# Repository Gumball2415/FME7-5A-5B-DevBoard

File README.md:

# FME7/S5A/S5B Development/Reproduction Cartridge Board

An Open-Source HardWare (OSHW) development/reproduction cartridge PCB designed for INES mapper 69.

## PCB Specifications

Note that this project is optimized for JLCPCB manufacturing, so you may have to modify the gerber export, remove the "JLCJLCJLCJLC" silkscreen text, etc.

- 2 layers
- 92mm x 56.7mm
- 1.20mm thickness
- ENIG-RoHS surface finish recommended; Gold fingers optional
- Light silkscreen, dark soldermask

## License

The PCB and schematics are licensed under the TAPR Open Hardware License ([www.tapr.org/OHL](http://www.tapr.org/OHL)). © Persune 2021

## Credits

- Lockster - Help and assistance with schematics
- lidnariq - Clarification on FME7 connections
- yoeynsf - Pixel art of Dagga
- plgDavid - Inspiration
- Special thanks to the NESDEV community, this project wouldn't have been possible without their extensive help and wiki.

## Support

Support me on [Ko-Fi](https://ko-fi.com/persune) to help me afford hardware development equipment and further improve this project!

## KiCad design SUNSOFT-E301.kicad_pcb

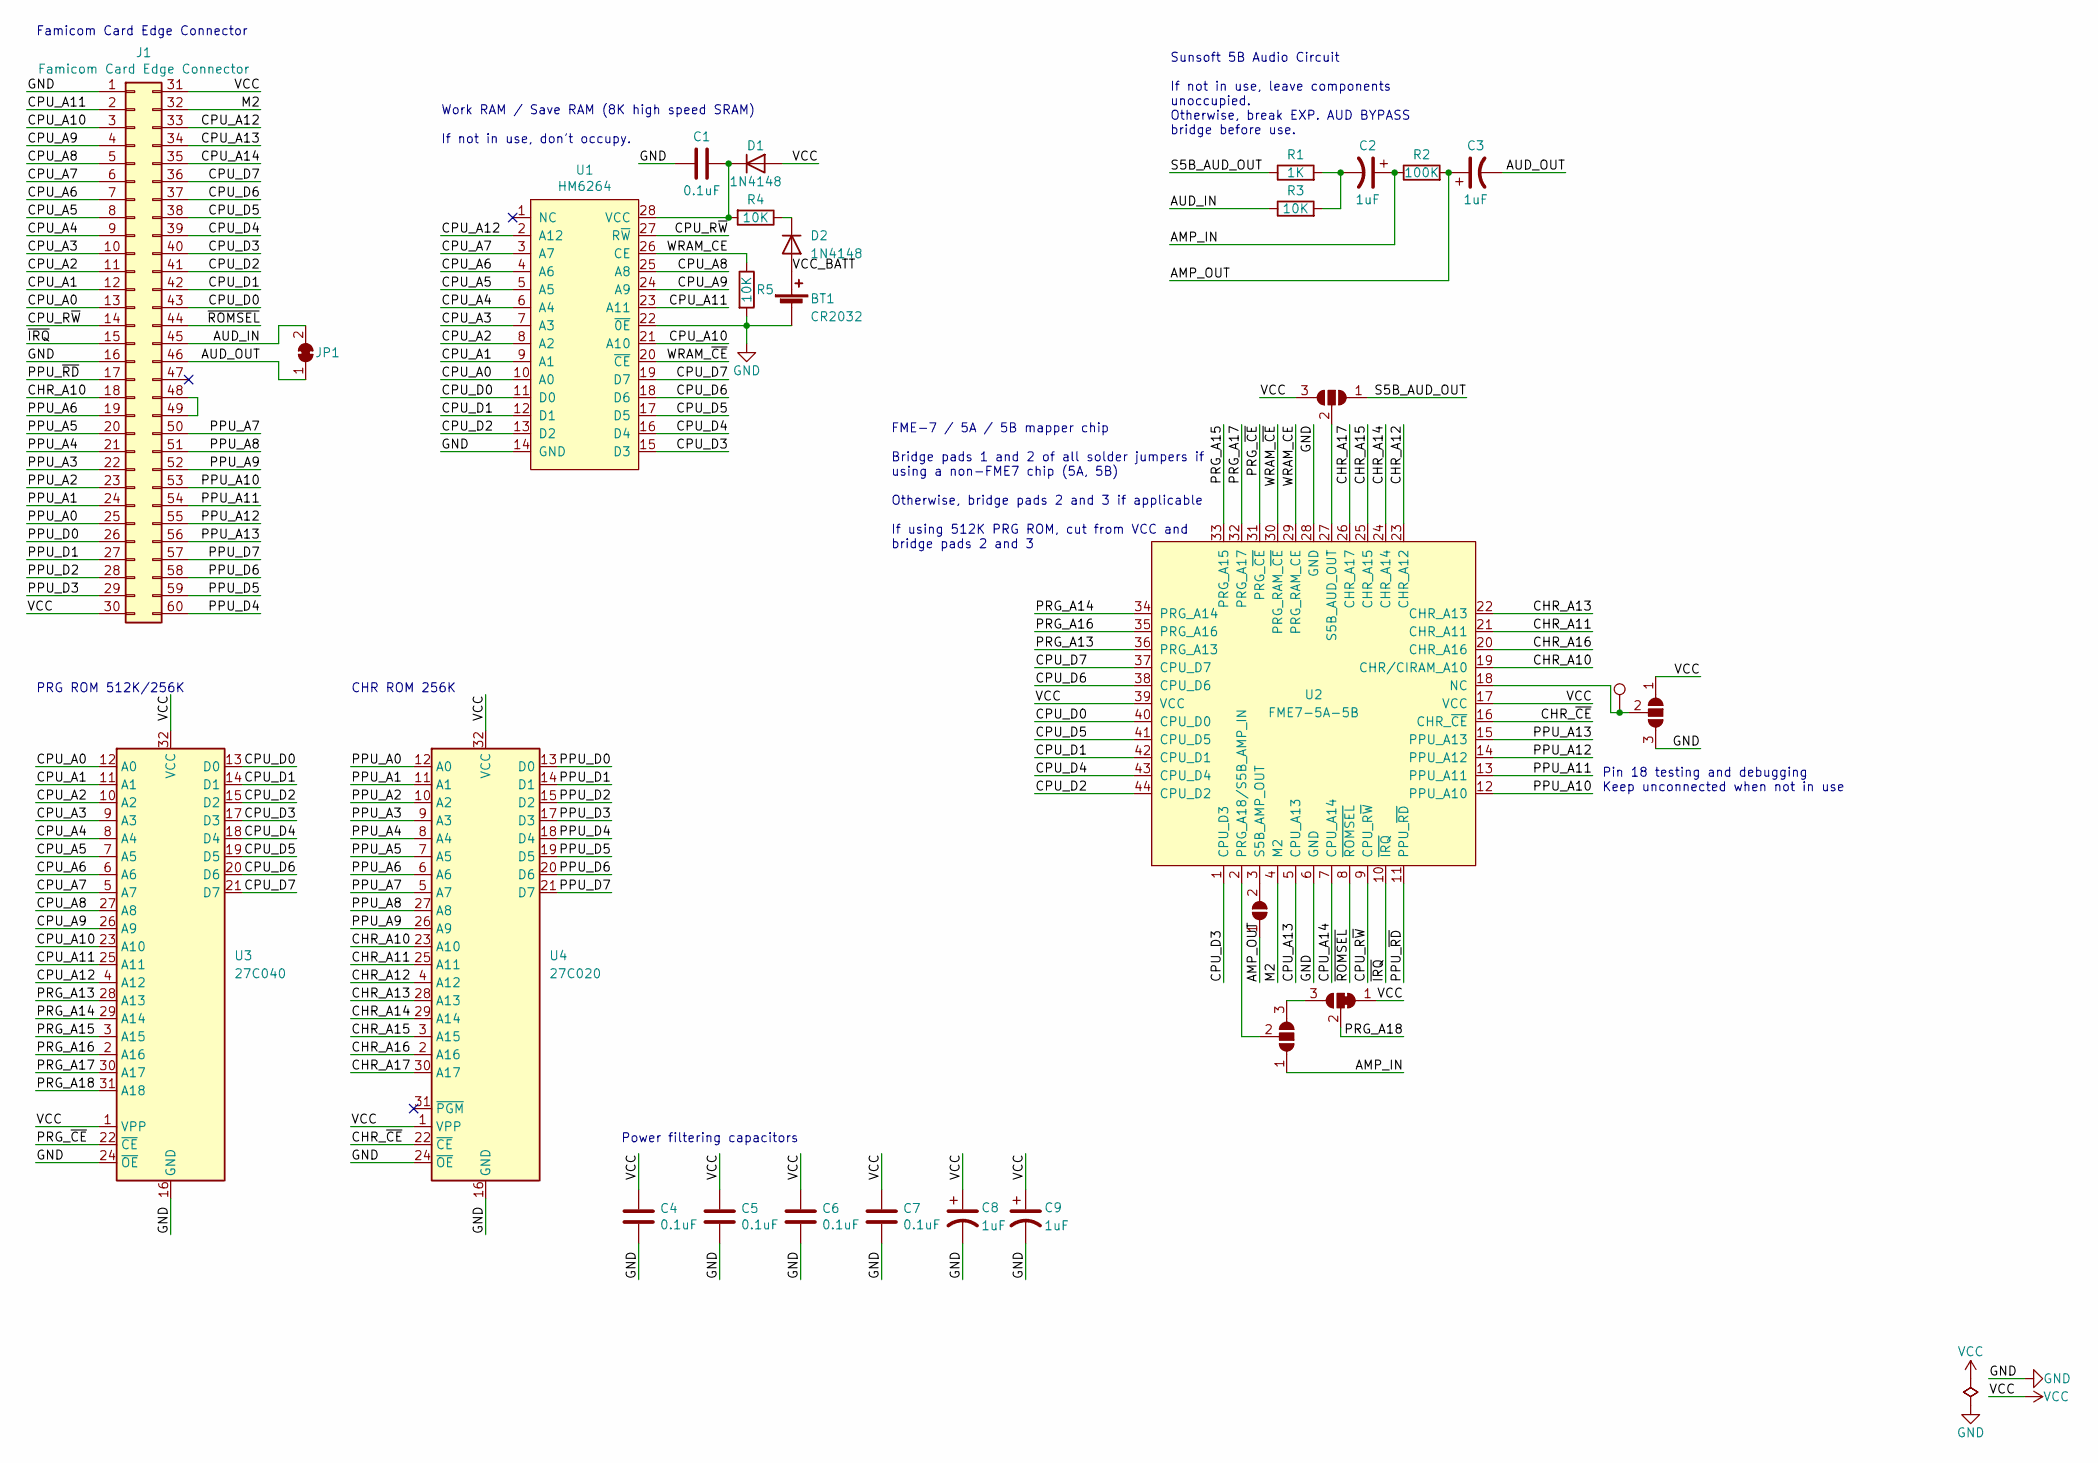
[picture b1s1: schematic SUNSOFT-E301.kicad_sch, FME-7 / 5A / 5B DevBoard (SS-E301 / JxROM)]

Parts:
BT1: CR2032; BS-02-A1AK006; LCSC C964746
C1, C4, C5, C6, C7: 0.1uF; C_0805_2012Metric; LCSC C779984
C2, C3, C8, C9: 1uF; CP_Elec_4x5.3; LCSC C249445
D1, D2: 1N4148; D_SOD-123; LCSC C2099
J1: Famicom Card Edge Connector; BBW-E301
JP1: SolderJumper_2_Bridged; SolderJumper-2_P1.3mm_Bridged_RoundedPad1.0x1.5mm
JP2, JP4, JP5: SolderJumper-3_P1.3mm_Open_RoundedPad1.0x1.5mm
JP3: SolderJumper-2_P1.3mm_Open_RoundedPad1.0x1.5mm
JP6: SolderJumper-3_P1.3mm_Bridged12_RoundedPad1.0x1.5mm
R1: 1K; R_0805_2012Metric; LCSC C441949
R2: 100K; R_0805_2012Metric; LCSC C441960
R3, R4, R5: 10K; R_0805_2012Metric; LCSC C441955
TP1: TestPoint_Pad_D1.0mm
U1: HM6264; DIP-28_W15.24mm; LCSC C72121
U2: FME7-5A-5B; Sunsoft-5
U3: 27C040; DIP-32_W15.24mm_Socket; LCSC C72122
U4: 27C020; DIP-32_W15.24mm_Socket; LCSC C72122

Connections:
/AMP_IN: C2.1, JP2.1 (A), R2.1
/AMP_OUT: C3.1, JP3.1 (A), R2.2
/AUD_IN: J1.45, JP1.2 (B), R3.1
/AUD_OUT: C3.2, J1.46, JP1.1 (A)
/CHR_A10: J1.18, U2.19 (CHR/CIRAM_A10), U4.23 (A10)
/CHR_A11: U2.21 (CHR_A11), U4.25 (A11)
/CHR_A12: U2.23 (CHR_A12), U4.4 (A12)
/CHR_A13: U2.22 (CHR_A13), U4.28 (A13)
/CHR_A14: U2.24 (CHR_A14), U4.29 (A14)
/CHR_A15: U2.25 (CHR_A15), U4.3 (A15)
/CHR_A16: U2.20 (CHR_A16), U4.2 (A16)
/CHR_A17: U2.26 (CHR_A17), U4.30 (A17)
/CHR_~CE: U2.16 (CHR_~CE), U4.22 (~CE)
/CPU_A0: J1.13, U1.10 (A0), U3.12 (A0)
/CPU_A1: J1.12, U1.9 (A1), U3.11 (A1)
/CPU_A2: J1.11, U1.8 (A2), U3.10 (A2)
/CPU_A3: J1.10, U1.7 (A3), U3.9 (A3)
/CPU_A4: J1.9, U1.6 (A4), U3.8 (A4)
/CPU_A5: J1.8, U1.5 (A5), U3.7 (A5)
/CPU_A6: J1.7, U1.4 (A6), U3.6 (A6)
/CPU_A7: J1.6, U1.3 (A7), U3.5 (A7)
/CPU_A8: J1.5, U1.25 (A8), U3.27 (A8)
/CPU_A9: J1.4, U1.24 (A9), U3.26 (A9)
/CPU_A10: J1.3, U1.21 (A10), U3.23 (A10)
/CPU_A11: J1.2, U1.23 (A11), U3.25 (A11)
/CPU_A12: J1.33, U1.2 (A12), U3.4 (A12)
/CPU_A13: J1.34, U2.5 (CPU_A13)
/CPU_A14: J1.35, U2.7 (CPU_A14)
/CPU_D0: J1.43, U1.11 (D0), U2.40 (CPU_D0), U3.13 (D0)
/CPU_D1: J1.42, U1.12 (D1), U2.42 (CPU_D1), U3.14 (D1)
/CPU_D2: J1.41, U1.13 (D2), U2.44 (CPU_D2), U3.15 (D2)
/CPU_D3: J1.40, U1.15 (D3), U2.1 (CPU_D3), U3.17 (D3)
/CPU_D4: J1.39, U1.16 (D4), U2.43 (CPU_D4), U3.18 (D4)
/CPU_D5: J1.38, U1.17 (D5), U2.41 (CPU_D5), U3.19 (D5)
/CPU_D6: J1.37, U1.18 (D6), U2.38 (CPU_D6), U3.20 (D6)
/CPU_D7: J1.36, U1.19 (D7), U2.37 (CPU_D7), U3.21 (D7)
/CPU_R~W: J1.14, U1.27 (R~W), U2.9 (CPU_R~W)
/M2: J1.32, U2.4 (M2)
/PPU_A0: J1.25, U4.12 (A0)
/PPU_A1: J1.24, U4.11 (A1)
/PPU_A2: J1.23, U4.10 (A2)
/PPU_A3: J1.22, U4.9 (A3)
/PPU_A4: J1.21, U4.8 (A4)
/PPU_A5: J1.20, U4.7 (A5)
/PPU_A6: J1.19, U4.6 (A6)
/PPU_A7: J1.50, U4.5 (A7)
/PPU_A8: J1.51, U4.27 (A8)
/PPU_A9: J1.52, U4.26 (A9)
/PPU_A10: J1.53, U2.12 (PPU_A10)
/PPU_A11: J1.54, U2.13 (PPU_A11)
/PPU_A12: J1.55, U2.14 (PPU_A12)
/PPU_A13: J1.56, U2.15 (PPU_A13)
/PPU_D0: J1.26, U4.13 (D0)
/PPU_D1: J1.27, U4.14 (D1)
/PPU_D2: J1.28, U4.15 (D2)
/PPU_D3: J1.29, U4.17 (D3)
/PPU_D4: J1.60, U4.18 (D4)
/PPU_D5: J1.59, U4.19 (D5)
/PPU_D6: J1.58, U4.20 (D6)
/PPU_D7: J1.57, U4.21 (D7)
/PPU_~RD: J1.17, U2.11 (PPU_~RD)
/PRG_A13: U2.36 (PRG_A13), U3.28 (A13)
/PRG_A14: U2.34 (PRG_A14), U3.29 (A14)
/PRG_A15: U2.33 (PRG_A15), U3.3 (A15)
/PRG_A16: U2.35 (PRG_A16), U3.2 (A16)
/PRG_A17: U2.32 (PRG_A17), U3.30 (A17)
/PRG_A18: JP6.2 (C), U3.31 (A18)
/PRG_~CE: U2.31 (PRG_~CE), U3.22 (~CE)
/S5B_AUD_OUT: JP4.1 (A), R1.1
/VCC_BATT: BT1.1 (+), D2.2 (A)
/WRAM_CE: R5.1, U1.26 (CE), U2.29 (PRG_RAM_CE)
/WRAM_~CE: U1.20 (~CE), U2.30 (PRG_RAM_~CE)
/~IRQ: J1.15, U2.10 (~IRQ)
/~ROMSEL: J1.44, U2.8 (~ROMSEL)
GND: BT1.2 (-), C1.1, C4.2, C5.2, C6.2, C7.2, C8.2, C9.2, J1.1, J1.16, JP5.3 (B), R5.2, U1.14 (GND), U1.22 (~0E), U2.6 (GND), U2.28 (GND), U3.16 (GND), U3.24 (~OE), U4.16 (GND), U4.24 (~OE)
unnamed: C1.2, D1.1 (K), R4.2, U1.28 (VCC)
unnamed: C2.2, R1.2, R3.2
unnamed: D2.1 (K), R4.1
unnamed: J1.48, J1.49
unnamed: JP2.2 (C), U2.2 (PRG_A18/S5B_AMP_IN)
unnamed: JP2.3 (B), JP6.3 (B)
unnamed: JP3.2 (B), U2.3 (S5B_AMP_OUT)
unnamed: JP4.2 (C), U2.27 (S5B_AUD_OUT)
unnamed: JP5.2 (C), TP1.1, U2.18 (NC)
VCC: C4.1, C5.1, C6.1, C7.1, C8.1, C9.1, D1.2 (A), J1.30, J1.31, JP4.3 (B), JP5.1 (A), JP6.1 (A), U2.17 (VCC), U2.39 (VCC), U3.1 (VPP), U3.32 (VCC), U4.1 (VPP), U4.32 (VCC)

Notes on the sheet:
Sunsoft 5B Audio Circuit If not in use, leave components unoccupied. Otherwise, break EXP. AUD BYPASS bridge before use.
Power filtering capacitors
Famicom Card Edge Connector
CHR ROM 256K
FME-7 / 5A / 5B mapper chip Bridge pads 1 and 2 of all solder jumpers if using a non-FME7 chip (5A, 5B) Otherwise, bridge pads 2 and 3 if applicable If using 512K PRG ROM, cut from VCC and bridge pads 2 and 3
Work RAM / Save RAM (8K high speed SRAM) If not in use, don't occupy.
Pin 18 testing and debugging Keep unconnected when not in use
PRG ROM 512K/256K

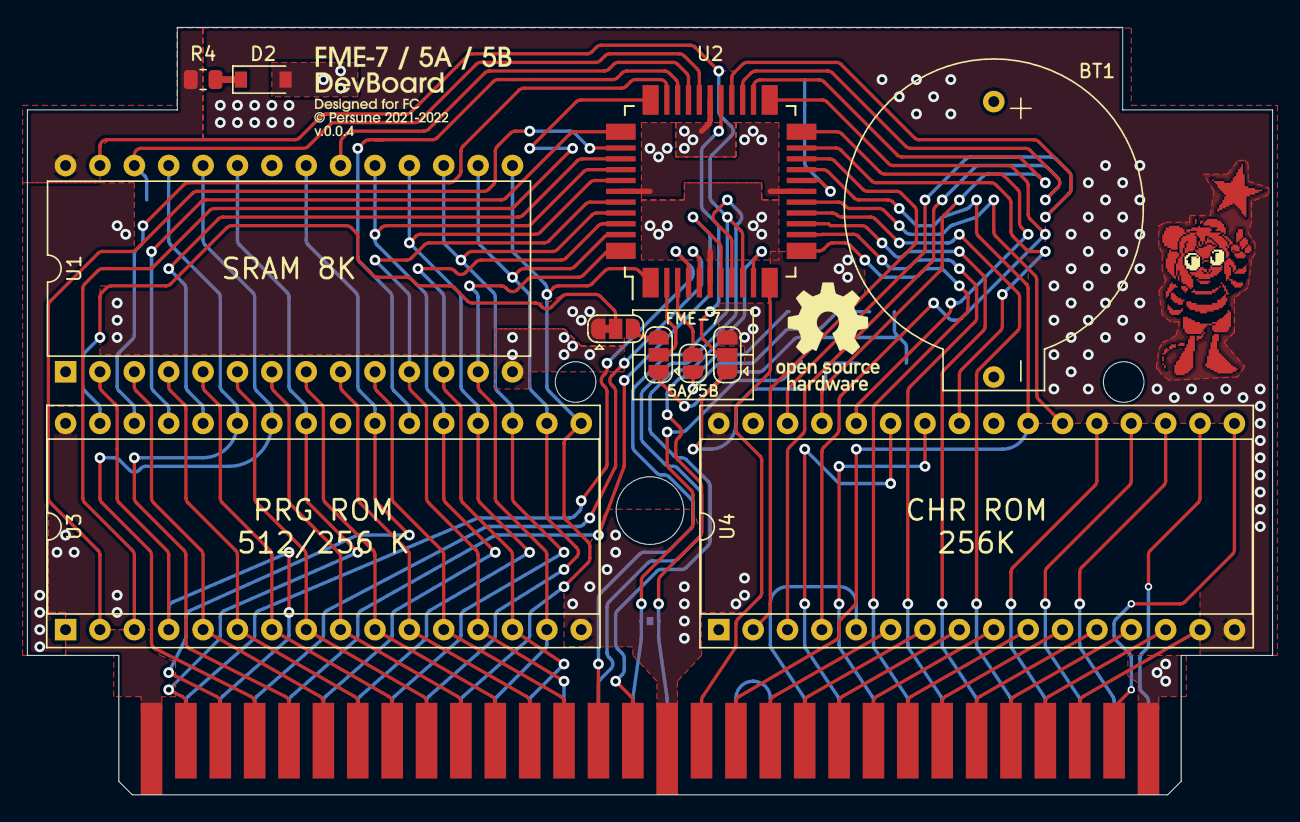
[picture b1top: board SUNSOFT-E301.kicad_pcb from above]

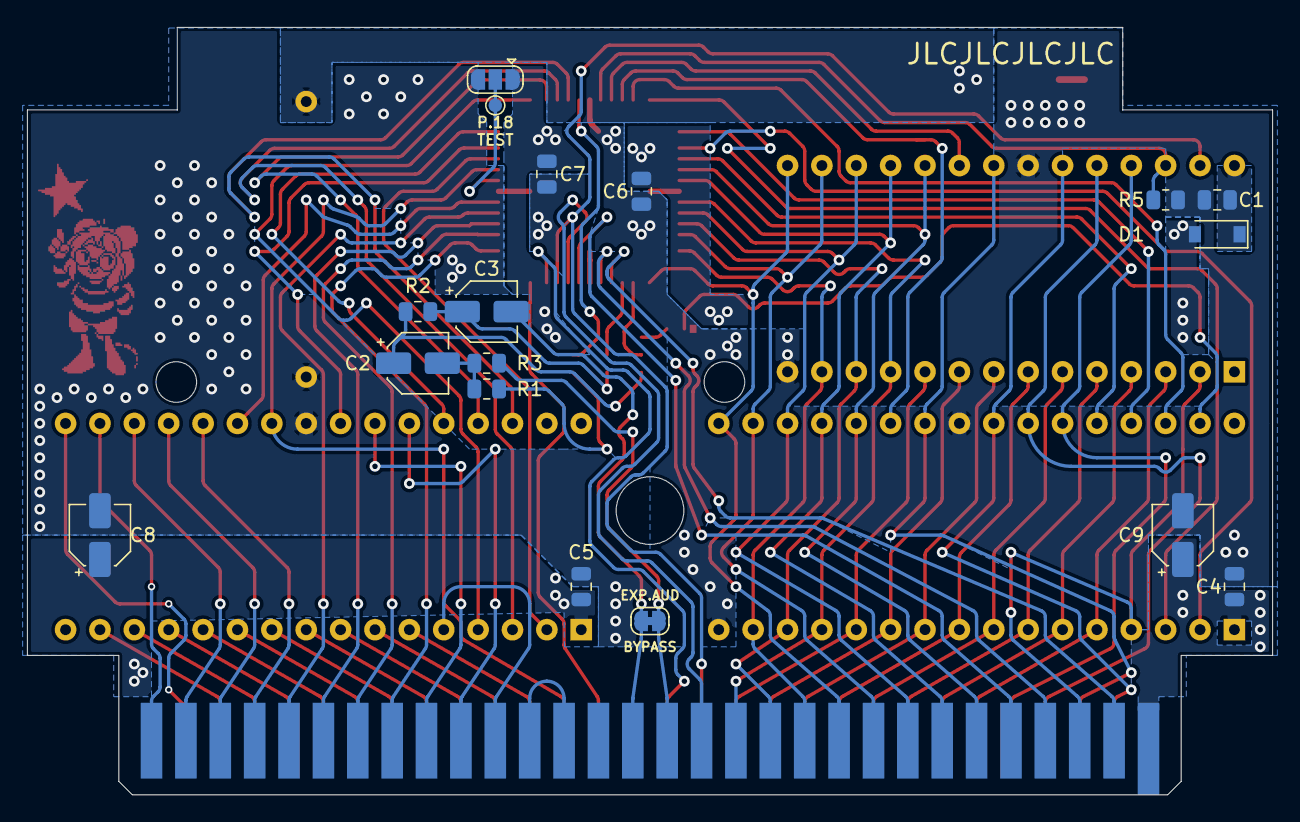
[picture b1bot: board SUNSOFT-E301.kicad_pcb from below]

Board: 2 copper layers, 92.0 x 56.7 mm, 30 parts (17 on the bottom side), 85 nets.

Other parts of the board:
Ref**: Val**; art_front

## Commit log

2021-12-06 add picture
2021-12-08 Add PCB specifications
2021-12-11 Revision 0.0.2
    - connect CIRAM A10
    - improve plane distribution
2021-12-11 Update README image
2021-12-17 Revision 0.0.3
    - updated outline to match Barcode World
    - added pixel sprite art by @yoeynsf
2021-12-27 KiCad 6.0
2022-03-11 Revision 0.0.4
2022-11-30 Add FUNDING.yml
